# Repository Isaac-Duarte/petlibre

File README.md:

# Wellfed

Wellfed frees the **PETLIBRO Granary PLAF103** pet feeder from the cloud. It gives the feeder replacement firmware, a command-line client and an optional self-hosted server, all running on your own network.

Wellfed is not affiliated with PETLIBRO, and it is not ready for everyday use yet. It is independent community research, tested on one feeder on our bench.

## Status

The replacement firmware feeds, joins Wi-Fi and talks to its clients on a real feeder. Here is what works today:

- **Feeding.** A supervised motor owner stops each feed on time and survives a power cut without feeding twice. The dispense button and the CLI both feed.
- **Connecting.** The feeder joins Wi-Fi, pairs over Bluetooth and serves an encrypted local API to the clients you pair.
- **Installing.** Stock firmware 1.1.15 installs Wellfed through its own updater, with no soldering. You can go back to stock over the air the same way.
- **Updating.** Over-the-air updates fall back to the previous image if the new one fails to start.

Schedules, the server's web UI and the Android app are not built yet. The [roadmap](docs/roadmap.md) has the full table and what comes next.

## Is Wellfed for you?

Wellfed may suit you if:

- you own a PLAF103 and want it to work without the vendor's cloud;
- you are comfortable with a command line and a self-built Rust toolchain;
- you want to help test, document or build a local-first feeder.

Don't use it yet if:

- a pet depends on the feeder for its meals. There are no schedules yet, and the firmware has not finished its long unattended run;
- you want a phone app. The Android app is not started;
- you have a different PETLIBRO model. Only the PLAF103 is supported, and a finding on one model never carries over to another;
- you can't afford to lose the feeder. Recovery from a bad flash needs UART access, and it is proven on one unit only.

## Documentation

The [documentation index](docs/README.md) lists every page. Good places to start:

| You want to… | Read |
| --- | --- |
| See what works and what's next | [Roadmap](docs/roadmap.md) |
| Install Wellfed over stock's updater | [Consumer installation](docs/firmware/consumer-installation.md) |
| Look up a word | [Glossary](docs/glossary.md) |
| Understand the product | [Product architecture](docs/firmware/product-architecture.md), [device API](docs/firmware/device-api.md), [the server](docs/server/README.md) |
| Understand the firmware | [Replacement firmware](docs/firmware/README.md), [OTA design](docs/firmware/ota-design.md), [bank policy](docs/firmware/bank-policy.md) |
| Learn the hardware | [PLAF103 device page](docs/devices/plaf103/README.md), [UART wiring](docs/devices/plaf103/uart.md), [flash layout](docs/devices/plaf103/flash-layout.md), [recovery](docs/devices/plaf103/recovery.md) |
| Contribute | [Contributing](CONTRIBUTING.md), [development setup](docs/development/README.md), [SDK builds](docs/development/firmware-builds.md), [writing docs](docs/development/writing.md) |

## Build and test

You don't need a feeder, vendor binaries or private research files to build, test and simulate the code.

Install Rust through rustup, GNU Make, CMake and a C compiler (for the Unicorn emulator the host tools link). The pinned Rust toolchain includes rustfmt, Clippy, and the ARM targets. On Linux:

```sh
cargo build --locked
make check
```

The first run downloads dependencies. Checks use host models and loopback networking. They never connect to a feeder, open serial ports or change firewall rules. SDK downloads and hardware operations are separate, explicit workflows.

## Repository layout

| Folder | Contents |
| --- | --- |
| `src/sdk/` | The SDK every firmware builds on: runtime, feeding core, hardware ports, board map and simulator ([firmware architecture](docs/firmware/README.md)) |
| `src/product/` | Product policy shared by the firmware and the server: the device protocol and the feeder's stores |
| `src/client/` | The clients the CLI, the server and the Android app share ([server design](docs/server/design.md#crates)) |
| `src/server/` | The owner's optional server ([the server](docs/server/README.md)) |
| `src/tools/` | Host tools, including the `wellfed` CLI ([tool list](src/tools/README.md)) |
| `src/firmware/wellfed/` | One crate per firmware: `feeder`, `qa`, `bringup` and `blink` ([firmware guide](src/firmware/wellfed/README.md)) |
| `src/firmware/vendor/` | The vendor SDK side: C hooks and ports, pinned SDK and toolchain locks, the stock layout, simulator scenarios and the image build (`make -C src/firmware/vendor`) |
| `src/firmware/devices/` | Per-device descriptions and layouts |
| `src/firmware/bench/` | The bench board's RP2040 firmware and its relay protocol crate ([bench firmware](src/firmware/bench/README.md)) |
| `src/hardware/bench/` | The Wellfed Bench board: KiCad project, fab outputs and enclosure ([bench board](src/hardware/bench/README.md)) |
| `src/web/` | Web frontends (a pnpm workspace): the bench page, the [well-fed.dev](docs/web/site.md) site, shared tokens and components, and API types generated from Rust. `make ui` builds them |
| `src/fuzz/` | Fuzz targets ([fuzzing](docs/development/README.md#fuzzing)) |
| `assets/` | Brand marks, design tokens, the feeder's 3D model and its renders ([assets](assets/README.md)) |
| `docs/` | Hardware findings, firmware design and contributor guides |
| `private/` | Ignored, contributor-owned secrets, evidence, dependencies and artifacts |

The existing `wellfed-*` crate names are kept for compatibility.

## License and provenance

First-party material is [MIT licensed](LICENSE), except the bench board's hardware design in `src/hardware/bench/`, which is [CERN-OHL-P](src/hardware/bench/LICENSE). Dependencies and vendor components keep their own licenses; see [third-party provenance](THIRD_PARTY.md).

This repository contains no vendor firmware or device backups. [Contributions](CONTRIBUTING.md) are welcome.

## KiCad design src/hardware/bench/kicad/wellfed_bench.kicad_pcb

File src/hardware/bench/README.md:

# Wellfed Bench board

The Wellfed Bench is an RP2040 USB-C board for recovering and developing on PETLIBRO feeders. It replaces the FT232R UART adapter and SH-UR04A relay board of the [relay bench](../../../docs/devices/plaf103/bench.md). Over one USB cable it shows up as a feeder UART bridge plus an `AT+CHn` relay port, so the bench tools can drive it the way they drive the relay board. This page covers the hardware: what is on the board, the files here, and how to order it. The firmware has [its own page](../../firmware/bench/README.md).

> [!NOTE]
> The board is designed but has never been built. Nothing here has been confirmed on hardware, and the bench tools do not use it yet.

> [!WARNING]
> Rev C is not ready to order. Its schematic adds two test pads, TP4 on `RUN` and TP5 on `QSPI_SS` (BOOT), that the board does not place or route yet: they sit outside the outline. Place and route them, run DRC, then export the gerbers.

## What it does

- **Feeder power.** A switched 5 V USB-A output (AP2171W, about 1.1 A limit) with an overcurrent flag, voltage and current sensing (INA181 on 50 mΩ).
- **Loader strap.** Holds feeder TX to GND through 4.7 kΩ, the ROM loader entry.
- **UART isolation.** A 74LVC2G125 buffer per direction, so the bridge cannot back-power a feeder that is off.
- **Aux power.** A second USB-C input, routed to the feeder by a TPS2116 when the host port cannot supply enough.
- **Feeder-alive sense.** Reads the feeder's TX level, so the board can tell that the D-cells still power a feeder whose 5 V is cut.
- **RECOVER button.** Power-cycles the feeder into its ROM loader without a host.
- **Room to grow.** 16 MB of flash (the firmware uses the first 2 MB), a 2×8 expansion header and an SWD header.

The relay channels, LEDs, buttons and pin map are listed in the [firmware page](../../firmware/bench/README.md#relay-port).

## Files

| Path | Contents |
| --- | --- |
| `kicad/` | The KiCad 10 project `wellfed_bench`: schematic, board and the `wellfed` symbol library |
| `fab/` | JLCPCB assembly files: the BOM and the placement file. The gerbers join them once rev C's test pads are placed |
| `enclosure/` | The OpenSCAD two-part enclosure and its button caps |

## Order from JLCPCB

1. Export the gerbers (F/B copper, paste, silkscreen and mask, Edge.Cuts) and the PTH and NPTH Excellon drill files from `kicad/wellfed_bench.kicad_pcb`, zip them, and upload the zip.
2. Turn on assembly, then upload `fab/wellfed_bench-BOM.csv` and `fab/wellfed_bench-CPL-jlcrot.csv`.
3. Set "Confirm Parts Placement" to Yes, and check every pin 1 and LED polarity in their review.

The `-jlcrot` placement file has JLCPCB's rotations and the J4 position corrected by hand. Regenerating it from KiCad loses those corrections, so edit it rather than replace it when parts move.

## Print the enclosure

The enclosure is two printed parts plus three button caps, held by four M3×12 screws into nuts pressed into the base. The assembly notes are at the top of the `.scad` file. Render each part to STL:

```sh
cd src/hardware/bench/enclosure
openscad -D 'part="base"' -o base.stl wellfed_bench_enclosure.scad
openscad -D 'part="lid"' -o lid.stl wellfed_bench_enclosure.scad
openscad -D 'part="button"' -o button.stl wellfed_bench_enclosure.scad
```

The STLs are not tracked. The base is sized for SLA resin, which cracks if screws self-tap into it.

## Edit the design

Open `kicad/wellfed_bench.kicad_pro` in KiCad 10. The board's logo is the one-color Wellfed lockup from [assets/brand](../../../assets/brand/README.md), flattened into hole-free polygons and mirrored on the back silkscreen.

After a board change, regenerate the gerbers and check the BOM and placement file against it before ordering.

## License

The board design, fab outputs and enclosure in this folder are licensed under the [CERN Open Hardware Licence v2, Permissive](LICENSE) (CERN-OHL-P). The firmware is MIT, like the rest of the repository.

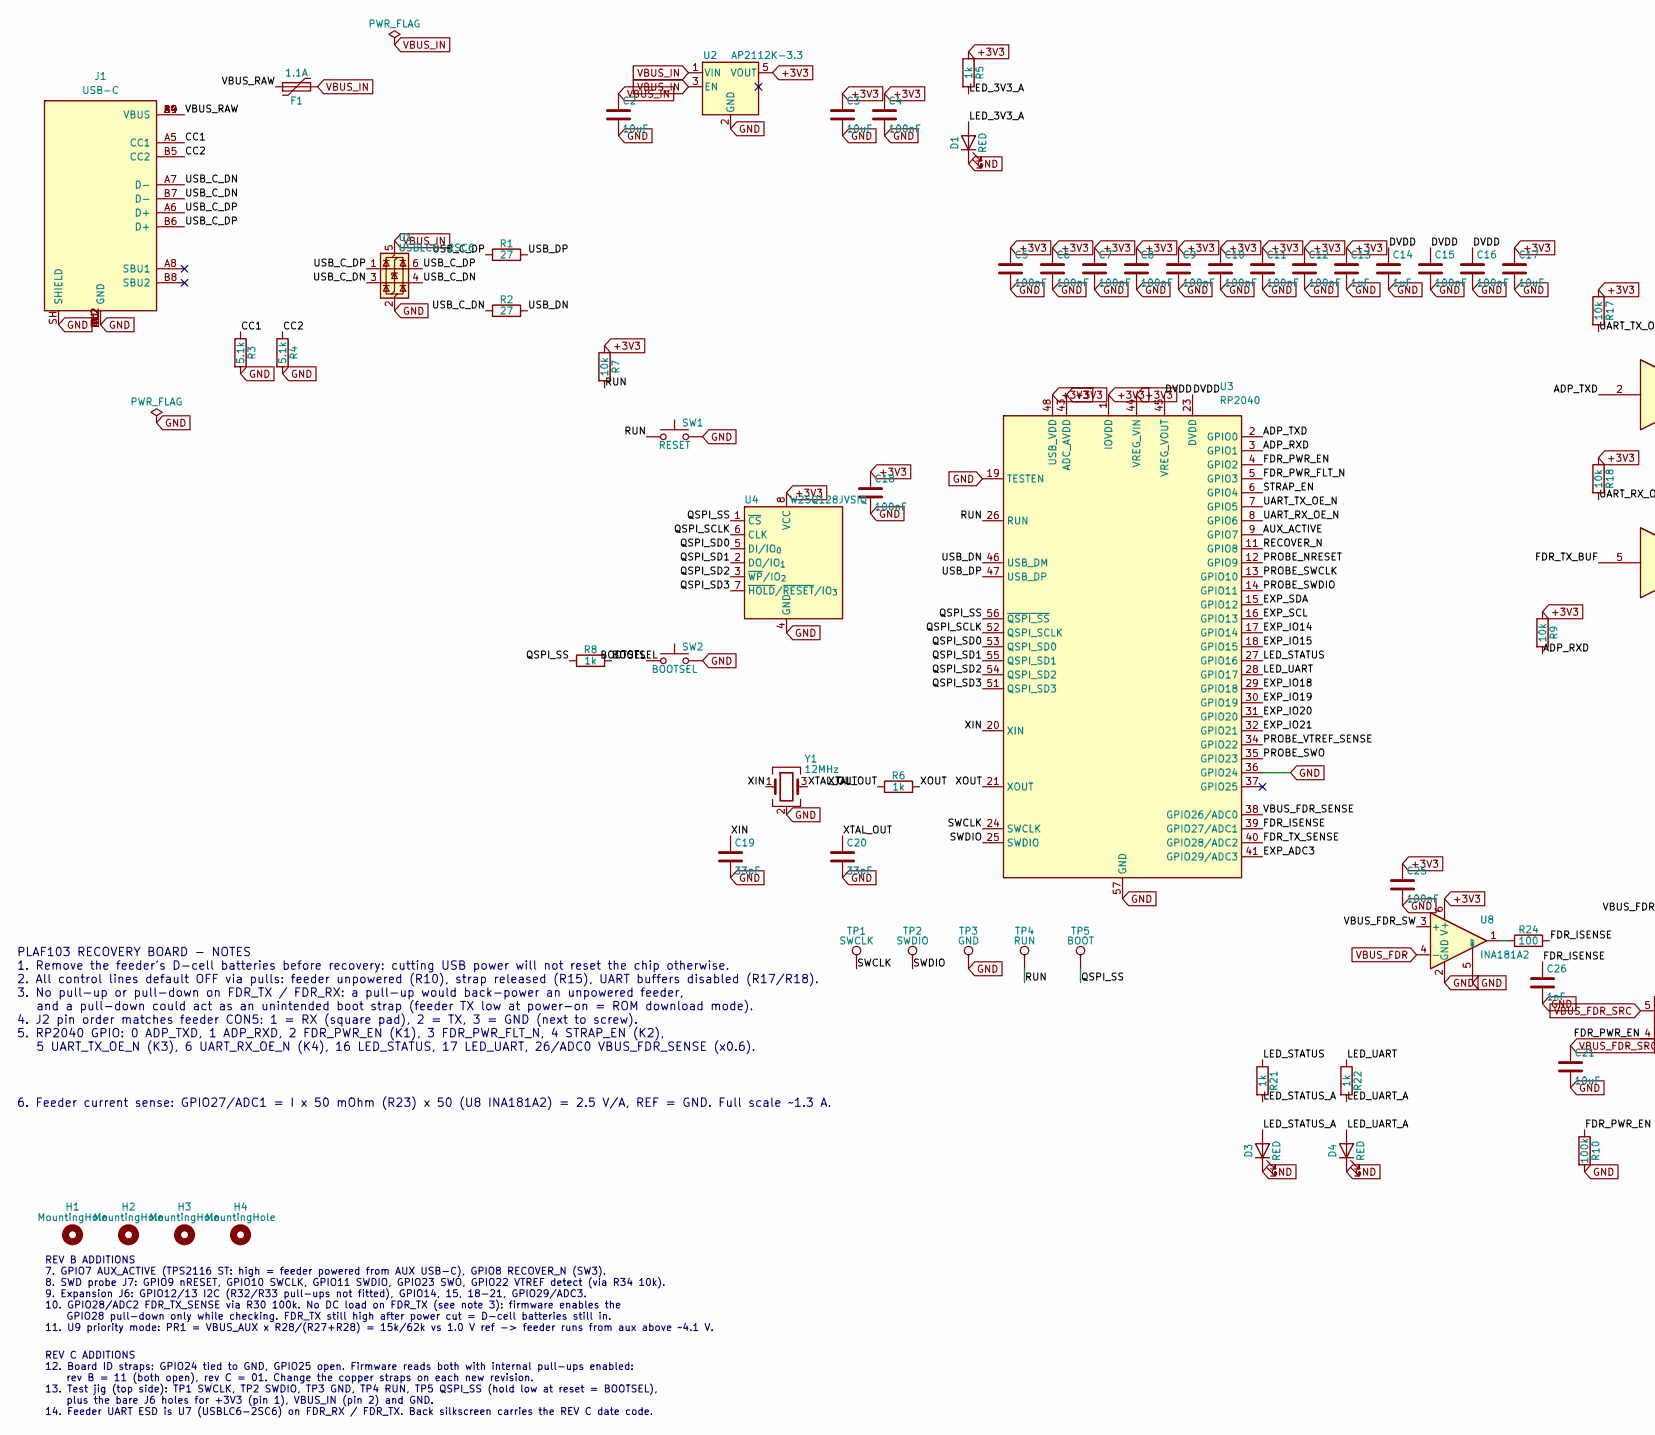
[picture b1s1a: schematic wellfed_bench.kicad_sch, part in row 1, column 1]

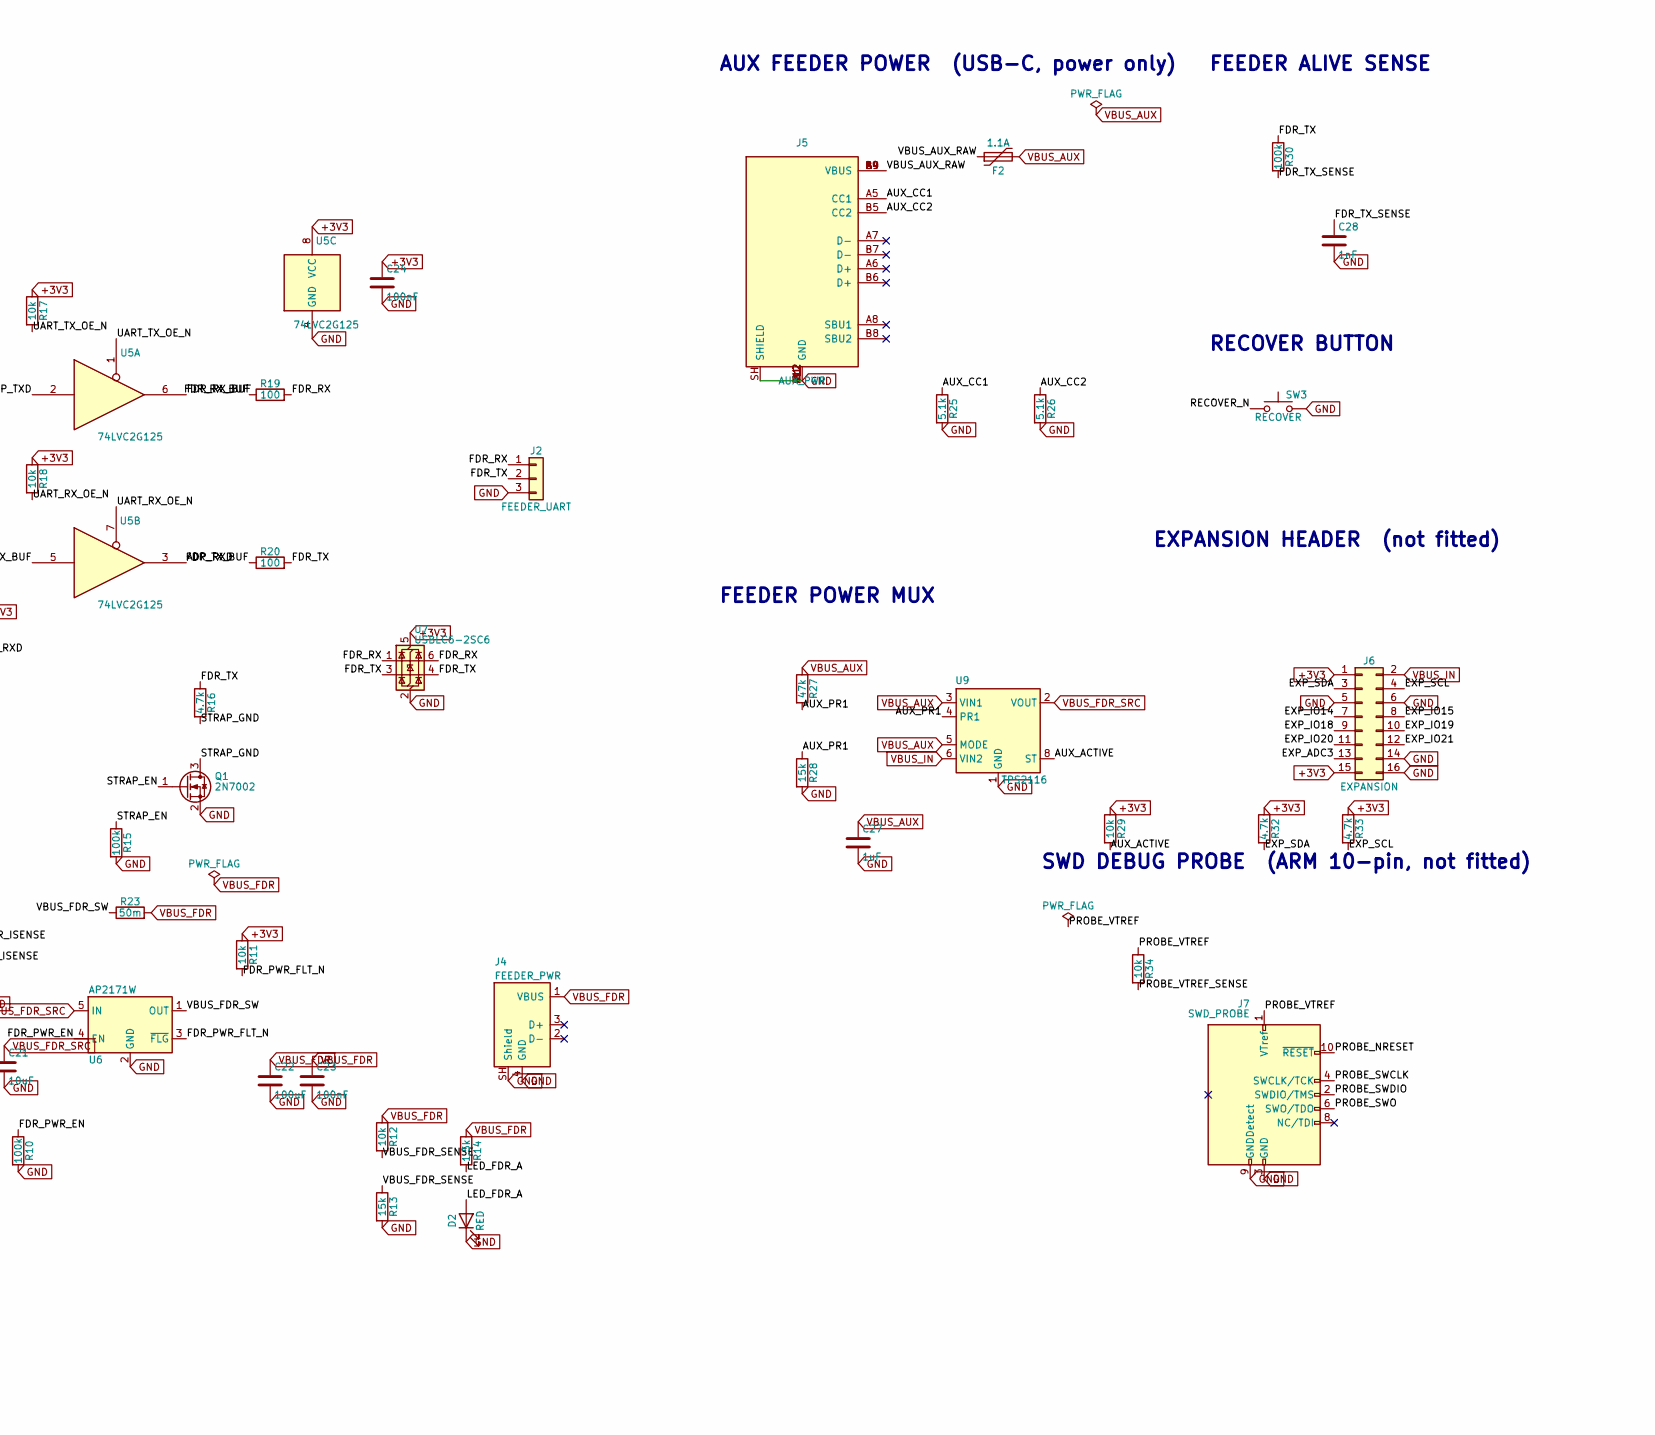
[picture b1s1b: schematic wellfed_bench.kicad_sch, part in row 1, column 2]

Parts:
C2, C3, C17: 10uF; C_0603_1608Metric; LCSC C19702
C4, C5, C6, C7, C8, C9, C10, C11, C12, C15, C16, C18, C23, C24, C25: 100nF; C_0402_1005Metric; LCSC C1525
C13, C14, C27: 1uF; C_0402_1005Metric; LCSC C52923
C19, C20: 33pF; C_0402_1005Metric; LCSC C1562
C21: 10uF; C_0402_1005Metric; LCSC C15525
C22: 100uF; C_1206_3216Metric; LCSC C15008
C26, C28: 1nF; C_0402_1005Metric; LCSC C1523
D1, D2, D3, D4: RED; LED_0603_1608Metric; LCSC C2286
F1, F2: 1.1A; Fuse_1206_3216Metric; MPN 1206L110THYR; LCSC C126818
H1, H2, H3, H4: MountingHole; MountingHole_3.2mm_M3
J1: USB-C; USB_C_Receptacle_HRO_TYPE-C-31-M-12; MPN TYPE-C-31-M-12; LCSC C165948
J2: FEEDER_UART; JST_PH_B3B-PH-K_1x03_P2.00mm_Vertical; MPN B3B-PH-K-S; LCSC C131339
J4: FEEDER_PWR; USB_A_Molex_67643_Horizontal; MPN 676430910; LCSC C2798029
J5: AUX_PWR; USB_C_Receptacle_HRO_TYPE-C-31-M-12; MPN TYPE-C-31-M-12; LCSC C165948
J6: EXPANSION; PinHeader_2x08_P2.54mm_Vertical
J7: SWD_PROBE; PinHeader_2x05_P1.27mm_Vertical
Q1: 2N7002; SOT-23; LCSC C8545
R1, R2: 27; R_0402_1005Metric; LCSC C25100
R3, R4, R25, R26: 5.1k; R_0402_1005Metric; LCSC C25905
R5, R6, R8, R21, R22: 1k; R_0402_1005Metric; LCSC C11702
R7, R9, R11, R12, R17, R18, R29, R34: 10k; R_0402_1005Metric; LCSC C25744
R10, R15, R30: 100k; R_0402_1005Metric; LCSC C25741
R13, R28: 15k; R_0402_1005Metric; LCSC C25756
R14: 1.5k; R_0402_1005Metric; LCSC C25867
R16, R32, R33: 4.7k; R_0402_1005Metric; LCSC C25900
R19, R20, R24: 100; R_0402_1005Metric; LCSC C25076
R23: 50m; R_1206_3216Metric; MPN FRM121WFR050TM; LCSC C7467249
R27: 47k; R_0402_1005Metric; LCSC C25792
SW1: RESET; SW_Push_1P1T_XKB_TS-1187A; LCSC C318884
SW2: BOOTSEL; SW_Push_1P1T_XKB_TS-1187A; LCSC C318884
SW3: RECOVER; SW_Push_1P1T_XKB_TS-1187A; LCSC C318884
TP1: SWCLK; TestPoint_Pad_D1.5mm
TP2: SWDIO; TestPoint_Pad_D1.5mm
TP3: GND; TestPoint_Pad_D1.5mm
TP4: RUN; TestPoint_Pad_D1.5mm
TP5: BOOT; TestPoint_Pad_D1.5mm
U1, U7: USBLC6-2SC6; SOT-23-6; LCSC C21713975
U2: AP2112K-3.3; SOT-23-5; LCSC C22365427
U3: RP2040; QFN-56-1EP_7x7mm_P0.4mm_EP3.2x3.2mm; LCSC C2040
U4: W25Q128JVSIQ; SOIC-8_5.3x5.3mm_P1.27mm; MPN W25Q128JVSIQ; LCSC C97521
U5: 74LVC2G125; VSSOP-8_2.3x2mm_P0.5mm; MPN SN74LVC2G125DCUR; LCSC C21404
U6: AP2171W; SOT-23-5; MPN AP2171WG-7; LCSC C110466
U8: INA181A2; SOT-23-6; MPN INA181A2IDBVR; LCSC C2058784
U9: TPS2116; SOT-583-8; MPN TPS2116DRLR; LCSC C3235557
Y1: 12MHz; Crystal_SMD_3225-4Pin_3.2x2.5mm; MPN X322512MSB4SI; LCSC C9002

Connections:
+3V3: C3.1, C4.1, C5.1, C6.1, C7.1, C8.1, C9.1, C10.1, C11.1, C12.1, C13.1, C17.1, C18.1, C24.1, C25.1, J6.1, J6.15, R5.1, R7.1, R9.1, R11.1, R17.1, R18.1, R29.1, R32.1, R33.1, U2.5 (VOUT), U3.1 (IOVDD), U3.10 (IOVDD), U3.22 (IOVDD), U3.33 (IOVDD), U3.42 (IOVDD), U3.43 (ADC_AVDD), U3.44 (VREG_VIN), U3.48 (USB_VDD), U3.49 (IOVDD), U4.8 (VCC), U5.8 (VCC), U7.5 (VBUS), U8.6 (V+)
/ADP_RXD: R9.2, U3.3 (GPIO1), U5.3
/ADP_TXD: U3.2 (GPIO0), U5.2
/AUX_ACTIVE: R29.2, U3.9 (GPIO7), U9.8 (ST)
/AUX_CC1: J5.A5 (CC1), R25.1
/AUX_CC2: J5.B5 (CC2), R26.1
/AUX_PR1: R27.2, R28.1, U9.4 (PR1)
/BOOTSEL: R8.2, SW2.1
/CC1: J1.A5 (CC1), R3.1
/CC2: J1.B5 (CC2), R4.1
/DVDD: C14.1, C15.1, C16.1, U3.23 (DVDD), U3.45 (VREG_VOUT), U3.50 (DVDD)
/EXP_ADC3: J6.13, U3.41 (GPIO29/ADC3)
/EXP_IO14: J6.7, U3.17 (GPIO14)
/EXP_IO15: J6.8, U3.18 (GPIO15)
/EXP_IO18: J6.9, U3.29 (GPIO18)
/EXP_IO19: J6.10, U3.30 (GPIO19)
/EXP_IO20: J6.11, U3.31 (GPIO20)
/EXP_IO21: J6.12, U3.32 (GPIO21)
/EXP_SCL: J6.4, R33.2, U3.16 (GPIO13)
/EXP_SDA: J6.3, R32.2, U3.15 (GPIO12)
/FDR_ISENSE: C26.1, R24.2, U3.39 (GPIO27/ADC1)
/FDR_PWR_EN: R10.1, U3.4 (GPIO2), U6.4 (EN)
/FDR_PWR_FLT_N: R11.2, U3.5 (GPIO3), U6.3 (~FLG)
/FDR_RX: J2.1, R19.2, U7.1 (I/O1), U7.6 (I/O1)
/FDR_RX_BUF: R19.1, U5.6
/FDR_TX: J2.2, R16.1, R20.2, R30.1, U7.3 (I/O2), U7.4 (I/O2)
/FDR_TX_BUF: R20.1, U5.5
/FDR_TX_SENSE: C28.1, R30.2, U3.40 (GPIO28/ADC2)
/LED_3V3_A: D1.2 (A), R5.2
/LED_FDR_A: D2.2 (A), R14.2
/LED_STATUS: R21.1, U3.27 (GPIO16)
/LED_STATUS_A: D3.2 (A), R21.2
/LED_UART: R22.1, U3.28 (GPIO17)
/LED_UART_A: D4.2 (A), R22.2
/PROBE_NRESET: J7.10 (~RESET), U3.12 (GPIO9)
/PROBE_SWCLK: J7.4 (SWCLK/TCK), U3.13 (GPIO10)
/PROBE_SWDIO: J7.2 (SWDIO/TMS), U3.14 (GPIO11)
/PROBE_SWO: J7.6 (SWO/TDO), U3.35 (GPIO23)
/PROBE_VTREF: J7.1 (VTref), R34.1
/PROBE_VTREF_SENSE: R34.2, U3.34 (GPIO22)
/QSPI_SCLK: U3.52 (QSPI_SCLK), U4.6 (CLK)
/QSPI_SD0: U3.53 (QSPI_SD0), U4.5 (DI/IO_{0})
/QSPI_SD1: U3.55 (QSPI_SD1), U4.2 (DO/IO_{1})
/QSPI_SD2: U3.54 (QSPI_SD2), U4.3 (~WP/IO_{2})
/QSPI_SD3: U3.51 (QSPI_SD3), U4.7 (~HOLD/~RESET/IO_{3})
/QSPI_SS: R8.1, TP5.1 (1_1), U3.56 (~QSPI_SS), U4.1 (~CS)
/RECOVER_N: SW3.1, U3.11 (GPIO8)
/RUN: R7.2, SW1.1, TP4.1 (1_1), U3.26 (RUN)
/STRAP_EN: Q1.1 (G), R15.1, U3.6 (GPIO4)
/STRAP_GND: Q1.3 (D), R16.2
/SWCLK: TP1.1 (1_1), U3.24 (SWCLK)
/SWDIO: TP2.1 (1_1), U3.25 (SWDIO)
/UART_RX_OE_N: R18.2, U3.8 (GPIO6), U5.7
/UART_TX_OE_N: R17.2, U3.7 (GPIO5), U5.1
/USB_C_DN: J1.A7 (D-), J1.B7 (D-), R2.1, U1.3 (I/O2), U1.4 (I/O2)
/USB_C_DP: J1.A6 (D+), J1.B6 (D+), R1.1, U1.1 (I/O1), U1.6 (I/O1)
/USB_DN: R2.2, U3.46 (USB_DM)
/USB_DP: R1.2, U3.47 (USB_DP)
/VBUS_AUX_RAW: F2.1, J5.A4 (VBUS), J5.A9 (VBUS), J5.B4 (VBUS), J5.B9 (VBUS)
/VBUS_FDR_SENSE: R12.2, R13.1, U3.38 (GPIO26/ADC0)
/VBUS_FDR_SW: R23.1, U6.1 (OUT), U8.3 (+)
/VBUS_RAW: F1.1, J1.A4 (VBUS), J1.A9 (VBUS), J1.B4 (VBUS), J1.B9 (VBUS)
/XIN: C19.1, U3.20 (XIN), Y1.1
/XOUT: R6.2, U3.21 (XOUT)
/XTAL_OUT: C20.1, R6.1, Y1.3
GND: C2.2, C3.2, C4.2, C5.2, C6.2, C7.2, C8.2, C9.2, C10.2, C11.2, C12.2, C13.2, C14.2, C15.2, C16.2, C17.2, C18.2, C19.2, C20.2, C21.2, C22.2, C23.2, C24.2, C25.2, C26.2, C27.2, C28.2, D1.1 (K), D2.1 (K), D3.1 (K), D4.1 (K), J1.A1 (GND), J1.A12 (GND), J1.B1 (GND), J1.B12 (GND), J1.SH (SHIELD), J2.3, J4.4 (GND), J4.SH (Shield), J5.A1 (GND), J5.A12 (GND), J5.B1 (GND), J5.B12 (GND), J5.SH (SHIELD), J6.5, J6.6, J6.14, J6.16, J7.3 (GND), J7.5 (GND), J7.9 (GNDDetect), Q1.2 (S), R3.2, R4.2, R10.2, R13.2, R15.2, R25.2, R26.2, R28.2, SW1.2, SW2.2, SW3.2, TP3.1 (1_1), U1.2 (GND), U2.2 (GND), U3.19 (TESTEN), U3.36 (GPIO24), U3.57 (GND), U4.4 (GND), U5.4 (GND), U6.2 (GND), U7.2 (GND), U8.2 (GND), U8.5 (REF), U9.1 (GND), Y1.2 (G), Y1.4 (G)
unnamed: R24.1, U8.1
VBUS_AUX: C27.1, F2.2, R27.1, U9.3 (VIN1), U9.5 (MODE)
VBUS_FDR: C22.1, C23.1, J4.1 (VBUS), R12.1, R14.1, R23.2, U8.4 (-)
VBUS_FDR_SRC: C21.1, U6.5 (IN), U9.2 (VOUT), U9.7 (VOUT)
VBUS_IN: C2.1, F1.2, J6.2, U1.5 (VBUS), U2.1 (VIN), U2.3 (EN), U9.6 (VIN2)

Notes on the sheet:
EXPANSION HEADER (not fitted)
6. Feeder current sense: GPIO27/ADC1 = I x 50 mOhm (R23) x 50 (U8 INA181A2) = 2.5 V/A, REF = GND. Full scale ~1.3 A.
FEEDER POWER MUX
REV B ADDITIONS 7. GPIO7 AUX_ACTIVE (TPS2116 ST: high = feeder powered from AUX USB-C), GPIO8 RECOVER_N (SW3). 8. SWD probe J7: GPIO9 nRESET, GPIO10 SWCLK, GPIO11 SWDIO, GPIO23 SWO, GPIO22 VTREF detect (via R34 10k). 9. Expansion J6: GPIO12/13 I2C (R32/R33 pull-ups not fitted), GPIO14, 15, 18-21, G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
FEEDER ALIVE SENSE
AUX FEEDER POWER (USB-C, power only)
PLAF103 RECOVERY BOARD - NOTES 1. Remove the feeder's D-cell batteries before recovery: cutting USB power will not reset the chip otherwise. 2. All control lines default OFF via pulls: feeder unpowered (R10), strap released (R15), UART buffers disabled (R17/R18). 3. No pull-up or pull-down on FDR_T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
SWD DEBUG PROBE (ARM 10-pin, not fitted)
REV C ADDITIONS 12. Board ID straps: GPIO24 tied to GND, GPIO25 open. Firmware reads both with internal pull-ups enabled: rev B = 11 (both open), rev C = 01. Change the copper straps on each new revision. 13. Test jig (top side): TP1 SWCLK, TP2 SWDIO, TP3 GND, TP4 RUN, TP5 QSPI_SS (hold low at rese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
RECOVER BUTTON

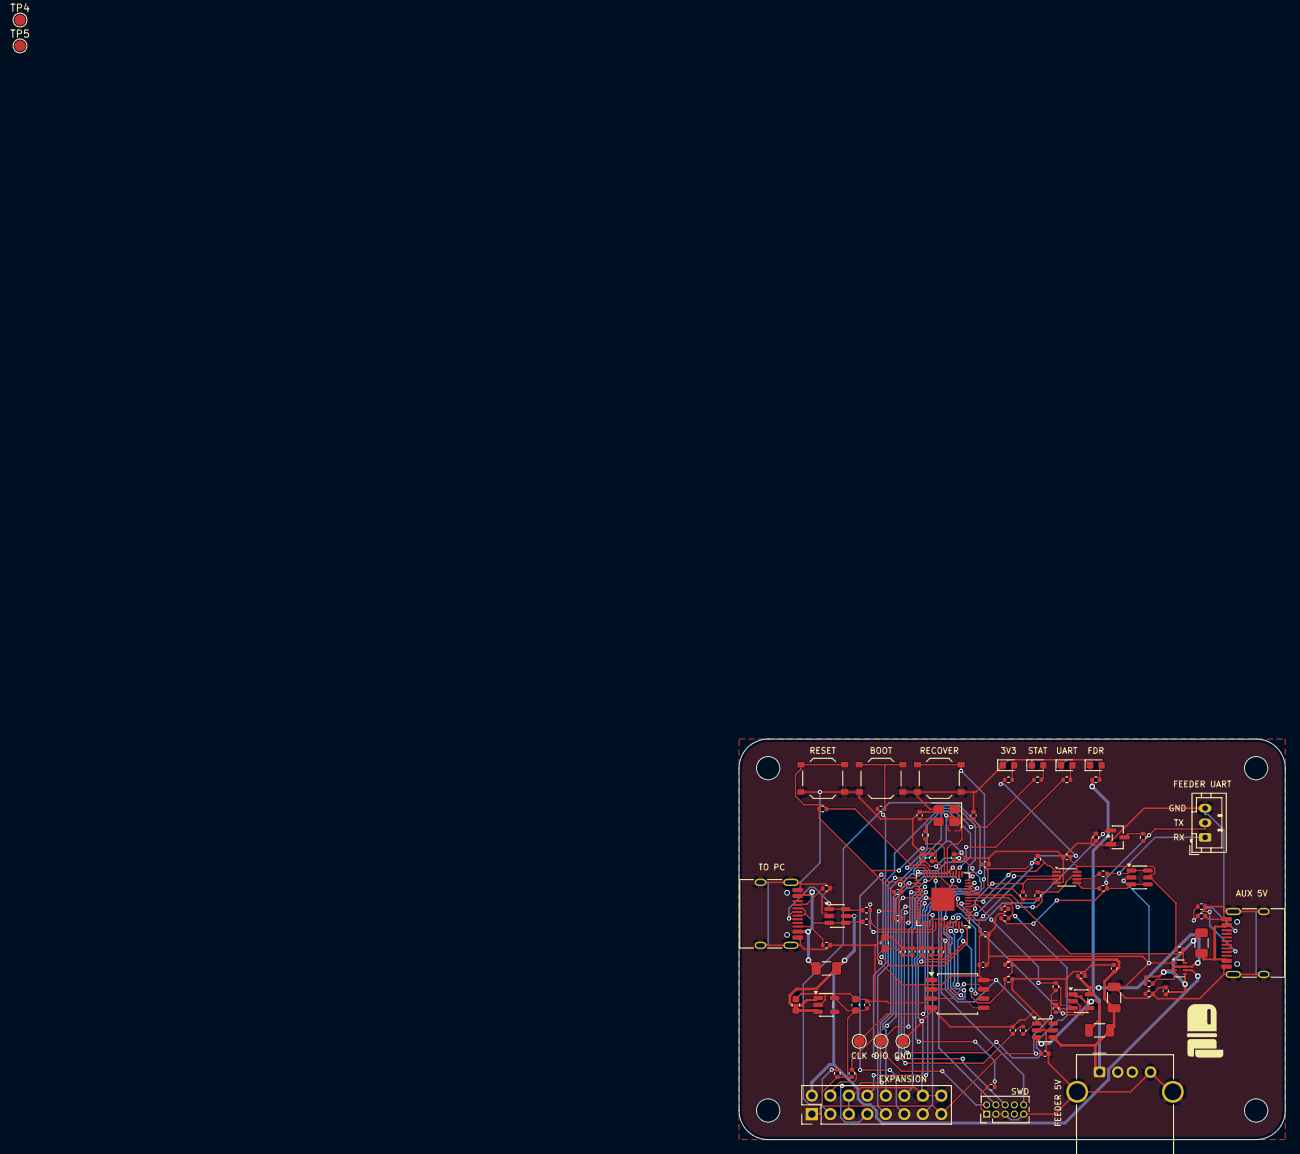
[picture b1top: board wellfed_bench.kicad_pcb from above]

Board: 2 copper layers, 75.0 x 55.0 mm, 95 parts (0 on the bottom side), 71 nets.

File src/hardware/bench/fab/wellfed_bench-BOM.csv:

"Comment","Designator","Footprint","LCSC Part #"
"10uF","C2,C3,C17","Capacitor_SMD:C_0603_1608Metric","C19702"
"100nF","C4,C5,C6,C7,C8,C9,C10,C11,C12,C15,C16,C18,C23,C24,C25","Capacitor_SMD:C_0402_1005Metric","C1525"
"1uF","C13,C14,C27","Capacitor_SMD:C_0402_1005Metric","C52923"
"10uF","C21","Capacitor_SMD:C_0402_1005Metric","C15525"
"33pF","C19,C20","Capacitor_SMD:C_0402_1005Metric","C1562"
"100uF","C22","Capacitor_SMD:C_1206_3216Metric","C15008"
"1nF","C26,C28","Capacitor_SMD:C_0402_1005Metric","C1523"
"RED","D1,D2,D3,D4","LED_SMD:LED_0603_1608Metric","C2286"
"1.1A","F1,F2","Fuse:Fuse_1206_3216Metric","C126818"
"USB-C","J1,J5","Connector_USB:USB_C_Receptacle_HRO_TYPE-C-31-M-12","C165948"
"FEEDER_UART","J2","Connector_JST:JST_PH_B3B-PH-K_1x03_P2.00mm_Vertical","C131339"
"FEEDER_PWR","J4","Connector_USB:USB_A_Molex_67643_Horizontal","C2798029"
"2N7002","Q1","Package_TO_SOT_SMD:SOT-23","C8545"
"27","R1,R2","Resistor_SMD:R_0402_1005Metric","C25100"
"5.1k","R3,R4,R25,R26","Resistor_SMD:R_0402_1005Metric","C25905"
"1k","R5,R6,R8,R21,R22","Resistor_SMD:R_0402_1005Metric","C11702"
"10k","R7,R9,R11,R12,R17,R18,R29,R34","Resistor_SMD:R_0402_1005Metric","C25744"
"15k","R28,R13","Resistor_SMD:R_0402_1005Metric","C25756"
"100k","R10,R15,R30","Resistor_SMD:R_0402_1005Metric","C25741"
"1.5k","R14","Resistor_SMD:R_0402_1005Metric","C25867"
"4.7k","R16","Resistor_SMD:R_0402_1005Metric","C25900"
"100","R19,R20,R24","Resistor_SMD:R_0402_1005Metric","C25076"
"50m","R23","Resistor_SMD:R_1206_3216Metric","C7467249"
"47k","R27","Resistor_SMD:R_0402_1005Metric","C25792"
"TS-1187A","SW1,SW2,SW3","Button_Switch_SMD:SW_Push_1P1T_XKB_TS-1187A","C318884"
"USBLC6-2SC6","U1,U7","Package_TO_SOT_SMD:SOT-23-6","C21713975"
"AP2112K-3.3","U2","Package_TO_SOT_SMD:SOT-23-5","C22365427"
"RP2040","U3","Package_DFN_QFN:QFN-56-1EP_7x7mm_P0.4mm_EP3.2x3.2mm","C2040"
"W25Q128JVSIQ","U4","Package_SO:SOIC-8_5.3x5.3mm_P1.27mm","C97521"
"74LVC2G125","U5","Package_SO:VSSOP-8_2.3x2mm_P0.5mm","C21404"
"AP2171W","U6","Package_TO_SOT_SMD:SOT-23-5","C110466"
"INA181A2","U8","Package_TO_SOT_SMD:SOT-23-6","C2058784"
"TPS2116","U9","Package_TO_SOT_SMD:SOT-583-8","C3235557"
"12MHz","Y1","Crystal:Crystal_SMD_3225-4Pin_3.2x2.5mm","C9002"
